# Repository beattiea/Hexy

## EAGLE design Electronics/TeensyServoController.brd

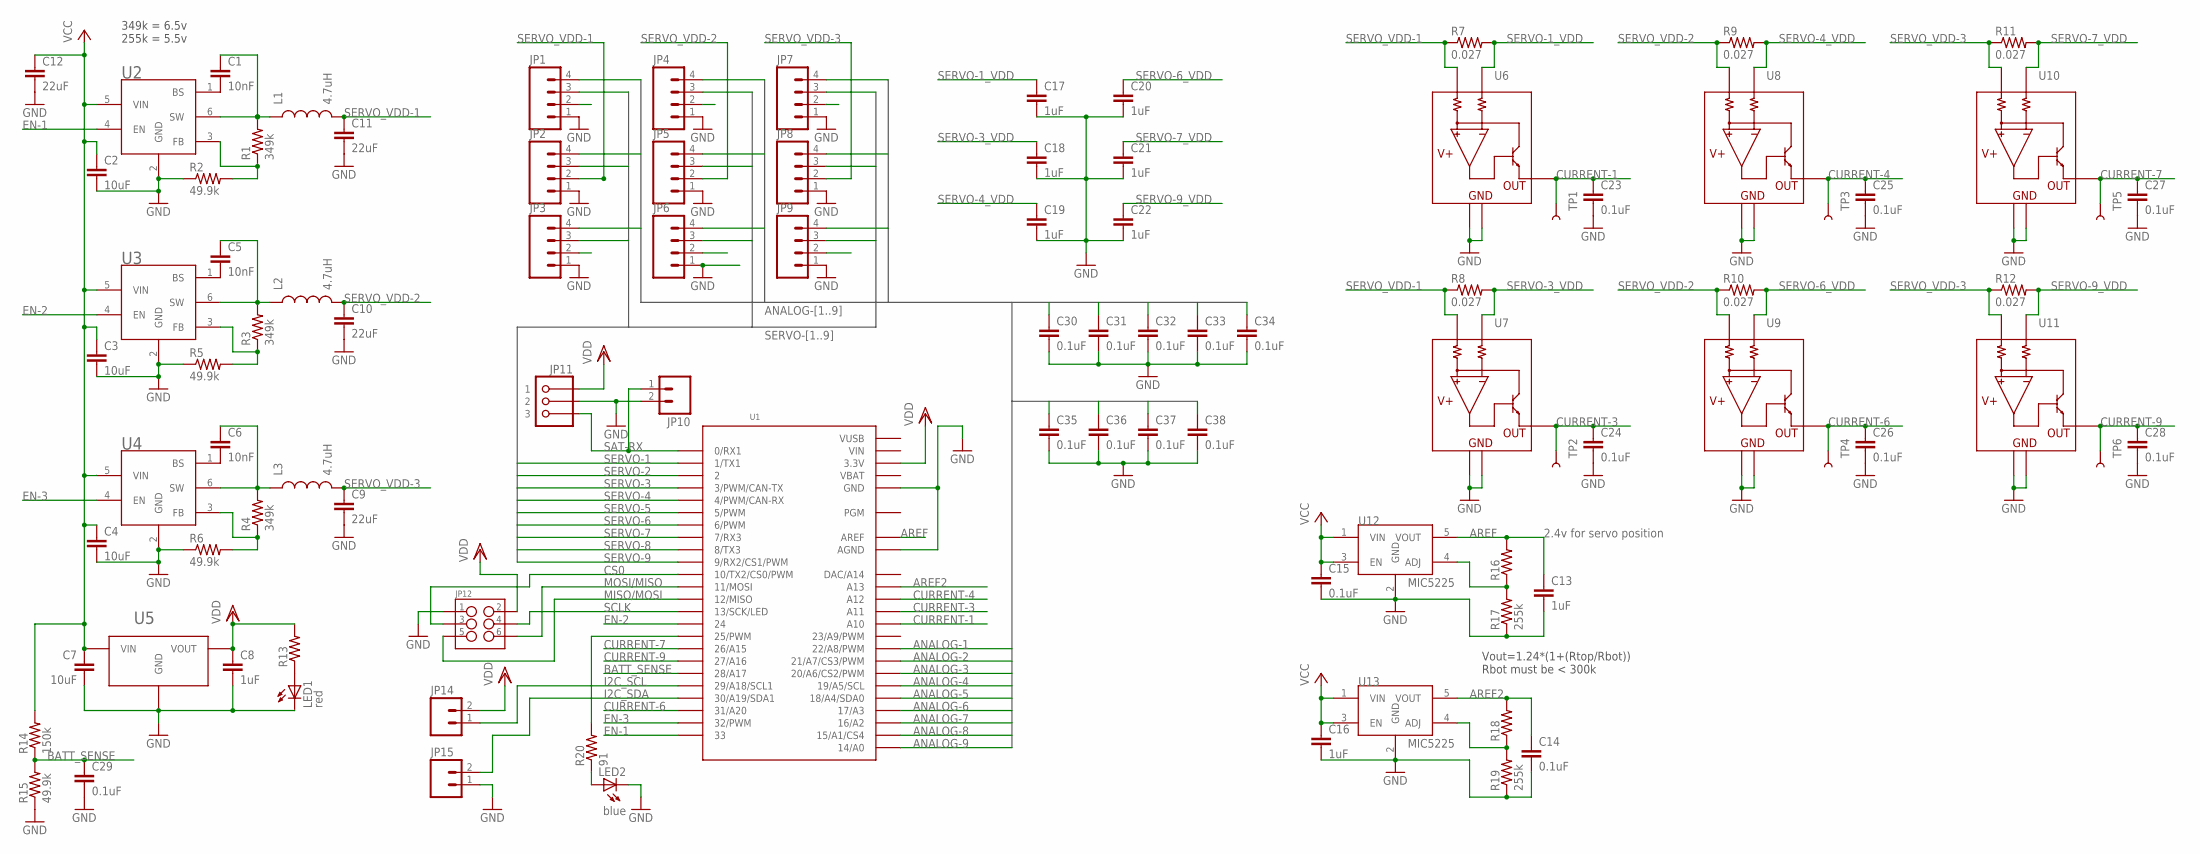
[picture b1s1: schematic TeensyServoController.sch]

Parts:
C1, C5, C6: 10nF; C0402
C2, C3, C4, C7: 10uF; C0805
C8, C13, C16, C17, C18, C19, C20, C21, C22: 1uF; C0603
C9, C10, C11: 22uF; C0603
C12: 22uF; C0805
C14, C23, C24, C25, C26, C27, C28, C29, C30, C31, C32, C33, C34, C35, C36, C37, C38: 0.1uF; C0402
C15: 0.1uF; C0603
JP1, JP2, JP3, JP4, JP5, JP6, JP7, JP8, JP9: M04PTH; 1X04
JP10, JP14, JP15: M02PTH; 1X02
JP11: 3-PIN_JST_ZH_PTH_CONNECTORRIGHT_ANGLE_PTH; 3-PIN_JST_ZH_CONNECTOR_TH
JP12: M03X22X3_SILK_SM; 2X3
L1, L2, L3: 4.7uH; 1008
LED1: red; LED-0603
LED2: blue; LED-0603
R1, R3, R4: 349k; R0402
R2, R5, R6, R15: 49.9k; R0402
R7, R8, R9, R10, R11, R12: 0.027; R0603
R13, R16, R18: R-US_R0402; R0402
R14: 150k; R0402
R17, R19: 255k; R0402
R20: 91; R0402
TP1, TP2, TP3, TP4, TP5, TP6: TEST-POINT3; PAD.03X.03
U1: TEENSY_3.1_ALLPINS; TEENSY_3.0_ALLPINS
U2, U3, U4: AP3211KTR-G1; SOT-23-6
U5: AP2210N-3.3TRG1; SOT23
U6, U7, U8, U9, U10, U11: TS1102; SOT23-5
U12, U13: MIC5225; SOT23-5

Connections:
ANALOG-1: C30.1, JP1.4, U1.22/A8 (22/A8/PWM)
ANALOG-2: C31.1, JP2.4, U1.21/A7 (21/A7/CS3/PWM)
ANALOG-3: C32.1, JP3.4, U1.20/A6 (20/A6/CS2/PWM)
ANALOG-4: C33.1, JP4.4, U1.19/A5 (19/A5/SCL)
ANALOG-5: C34.1, JP5.4, U1.18/A4 (18/A4/SDA0)
ANALOG-6: C35.1, JP6.4, U1.17/A3
ANALOG-7: C36.1, JP7.4, U1.16/A2
ANALOG-8: C37.1, JP8.4, U1.15/A1 (15/A1/CS4)
ANALOG-9: C38.1, JP9.4, U1.14/A0
AREF: C13.1, R16.2, U1.AREF, U12.5 (VOUT)
AREF2: C14.1, R18.2, U1.A13, U13.5 (VOUT)
BATT_SENSE: C29.1, R14.1, R15.2, U1.28 (28/A17)
CS0: JP12.3, U1.10 (10/TX2/CS0/PWM)
CURRENT-1: C23.1, TP1.P$1, U1.A10, U6.3 (OUT)
CURRENT-3: C24.1, TP2.P$1, U1.A11, U7.3 (OUT)
CURRENT-4: C25.1, TP3.P$1, U1.A12, U8.3 (OUT)
CURRENT-6: C26.1, TP4.P$1, U1.31 (31/A20), U9.3 (OUT)
CURRENT-7: C27.1, TP5.P$1, U1.26 (26/A15), U10.3 (OUT)
CURRENT-9: C28.1, TP6.P$1, U1.27 (27/A16), U11.3 (OUT)
EN-1: U1.33, U2.4 (EN)
EN-2: U1.24, U3.4 (EN)
EN-3: U1.32 (32/PWM), U4.4 (EN)
GND: C2.2, C3.2, C4.2, C7.2, C8.2, C9.2, C10.2, C11.2, C12.2, C13.2, C14.2, C15.2, C16.2, C17.2, C18.2, C19.2, C20.2, C21.2, C22.2, C23.2, C24.2, C25.2, C26.2, C27.2, C28.2, C29.2, C30.2, C31.2, C32.2, C33.2, C34.2, C35.2, C36.2, C37.2, C38.2, JP1.1, JP2.1, JP3.1, JP4.1, JP5.1, JP6.1, JP7.1, JP8.1, JP9.1, JP10.2, JP11.P$2 (2), JP12.1, JP15.1, LED1.C, LED2.C, R2.1, R5.1, R6.1, R15.1, R17.1, R19.1, U1.AGND, U1.GND, U1.GND1 (GND), U1.GND2 (GND), U2.2 (GND), U3.2 (GND), U4.2 (GND), U5.P$1 (GND), U6.1 (GND), U6.2, U7.1 (GND), U7.2, U8.1 (GND), U8.2, U9.1 (GND), U9.2, U10.1 (GND), U10.2, U11.1 (GND), U11.2, U12.2 (GND), U13.2 (GND)
I2C_SCL: JP14.1, U1.29 (29/A18/SCL1)
I2C_SDA: JP15.2, U1.30 (30/A19/SDA1)
MISO/MOSI: JP12.5, U1.12 (12/MISO)
MOSI/MISO: JP12.6, U1.11 (11/MOSI)
unnamed: LED1.A, R13.1
unnamed: R1.1, R2.2, U2.3 (FB)
unnamed: R16.1, R17.2, U12.4 (ADJ)
unnamed: R20.2, U1.25 (25/PWM)
unnamed: R18.1, R19.2, U13.4 (ADJ)
unnamed: LED2.A, R20.1
unnamed: C5.1, L2.P$1 (1), R3.2, U3.6 (SW)
unnamed: C1.1, L1.P$1 (1), R1.2, U2.6 (SW)
unnamed: C1.2, U2.1 (BS)
unnamed: R4.1, R6.2, U4.3 (FB)
unnamed: C5.2, U3.1 (BS)
unnamed: R3.1, R5.2, U3.3 (FB)
unnamed: C6.2, U4.1 (BS)
unnamed: C6.1, L3.P$1 (1), R4.2, U4.6 (SW)
SAT-RX: JP10.1, JP11.P$3 (3), U1.0 (0/RX1)
SCLK: JP12.4, U1.13 (13/SCK/LED)
SERVO-1: JP1.3, U1.1 (1/TX1)
SERVO-1_VDD: C17.1, JP1.2, R7.2, U6.4 (RS-)
SERVO-2: JP2.3, U1.2
SERVO-3: JP3.3, U1.3 (3/PWM/CAN-TX)
SERVO-3_VDD: C18.1, JP3.2, R8.2, U7.4 (RS-)
SERVO-4: JP4.3, U1.4 (4/PWM/CAN-RX)
SERVO-4_VDD: C19.1, JP4.2, R9.2, U8.4 (RS-)
SERVO-5: JP5.3, U1.5 (5/PWM)
SERVO-6: JP6.3, U1.6 (6/PWM)
SERVO-6_VDD: C20.1, JP6.2, R10.2, U9.4 (RS-)
SERVO-7: JP7.3, U1.7 (7/RX3)
SERVO-7_VDD: C21.1, JP7.2, R11.2, U10.4 (RS-)
SERVO-8: JP8.3, U1.8 (8/TX3)
SERVO-9: JP9.3, U1.9 (9/RX2/CS1/PWM)
SERVO-9_VDD: C22.1, JP9.2, R12.2, U11.4 (RS-)
SERVO_VDD-1: C11.1, JP2.2, L1.P$2 (2), R7.1, R8.1, U6.5 (RS+), U7.5 (RS+)
SERVO_VDD-2: C10.1, JP5.2, L2.P$2 (2), R9.1, R10.1, U8.5 (RS+), U9.5 (RS+)
SERVO_VDD-3: C9.1, JP8.2, L3.P$2 (2), R11.1, R12.1, U10.5 (RS+), U11.5 (RS+)
VBAT: U1.VBAT
VCC: C2.1, C3.1, C4.1, C7.1, C12.1, C15.1, C16.1, R14.2, U2.5 (VIN), U3.5 (VIN), U4.5 (VIN), U5.P$3 (VIN), U12.1 (VIN), U12.3 (EN), U13.1 (VIN), U13.3 (EN)
VDD: C8.1, JP11.P$1 (1), JP12.2, JP14.2, R13.2, U1.3.3V, U1.3.3V1 (3.3V), U1.3.3V2 (3.3V), U1.VIN, U5.P$2 (VOUT)
VUSB: U1.VUSB

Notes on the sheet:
349k = 6.5v 255k = 5.5v
Vout=1.24*(1+(Rtop/Rbot)) Rbot must be < 300k
2.4v for servo position

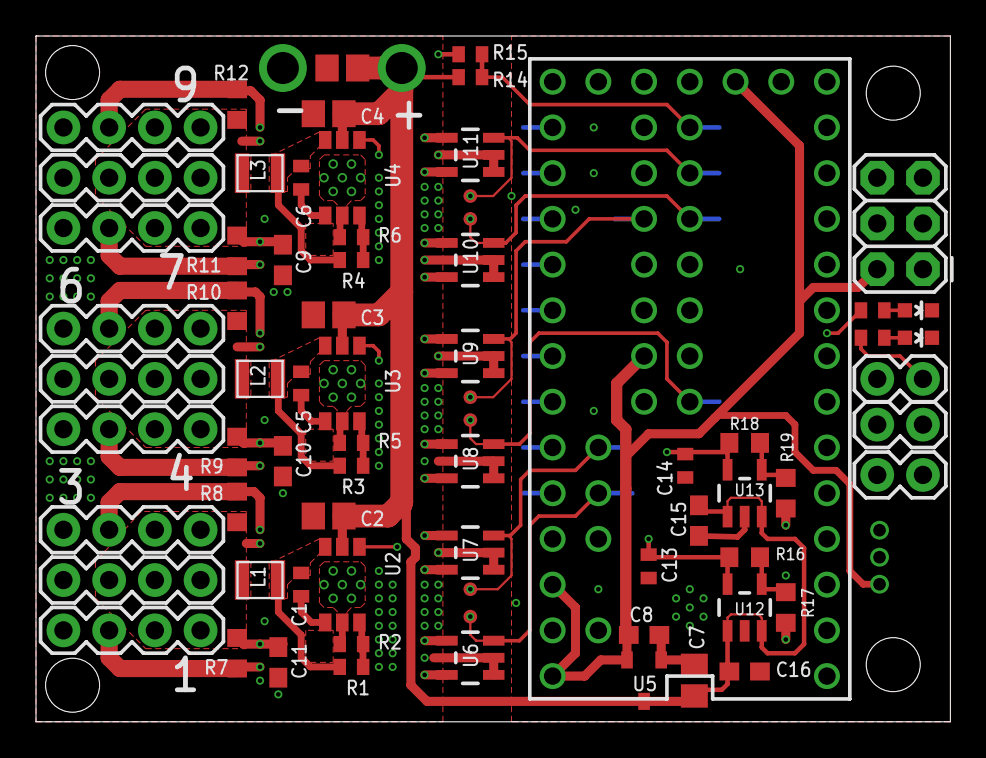
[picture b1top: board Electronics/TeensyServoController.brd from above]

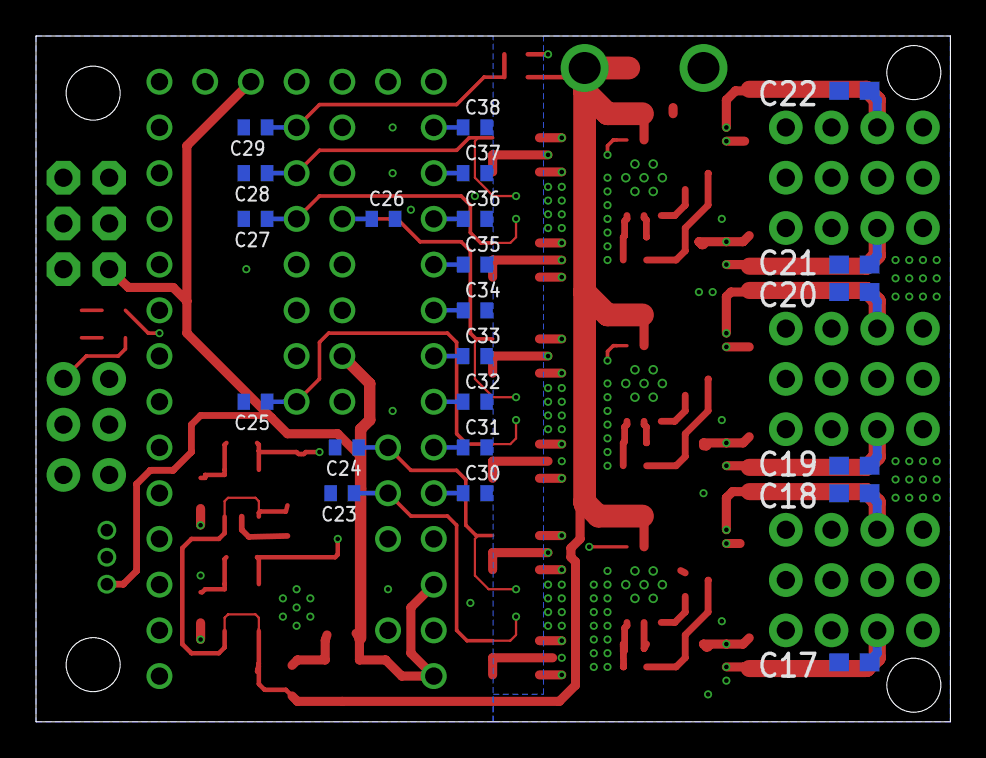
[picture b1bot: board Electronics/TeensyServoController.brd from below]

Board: 4 copper layers, 50.8 x 38.1 mm, 96 parts (22 on the bottom side), 63 nets.

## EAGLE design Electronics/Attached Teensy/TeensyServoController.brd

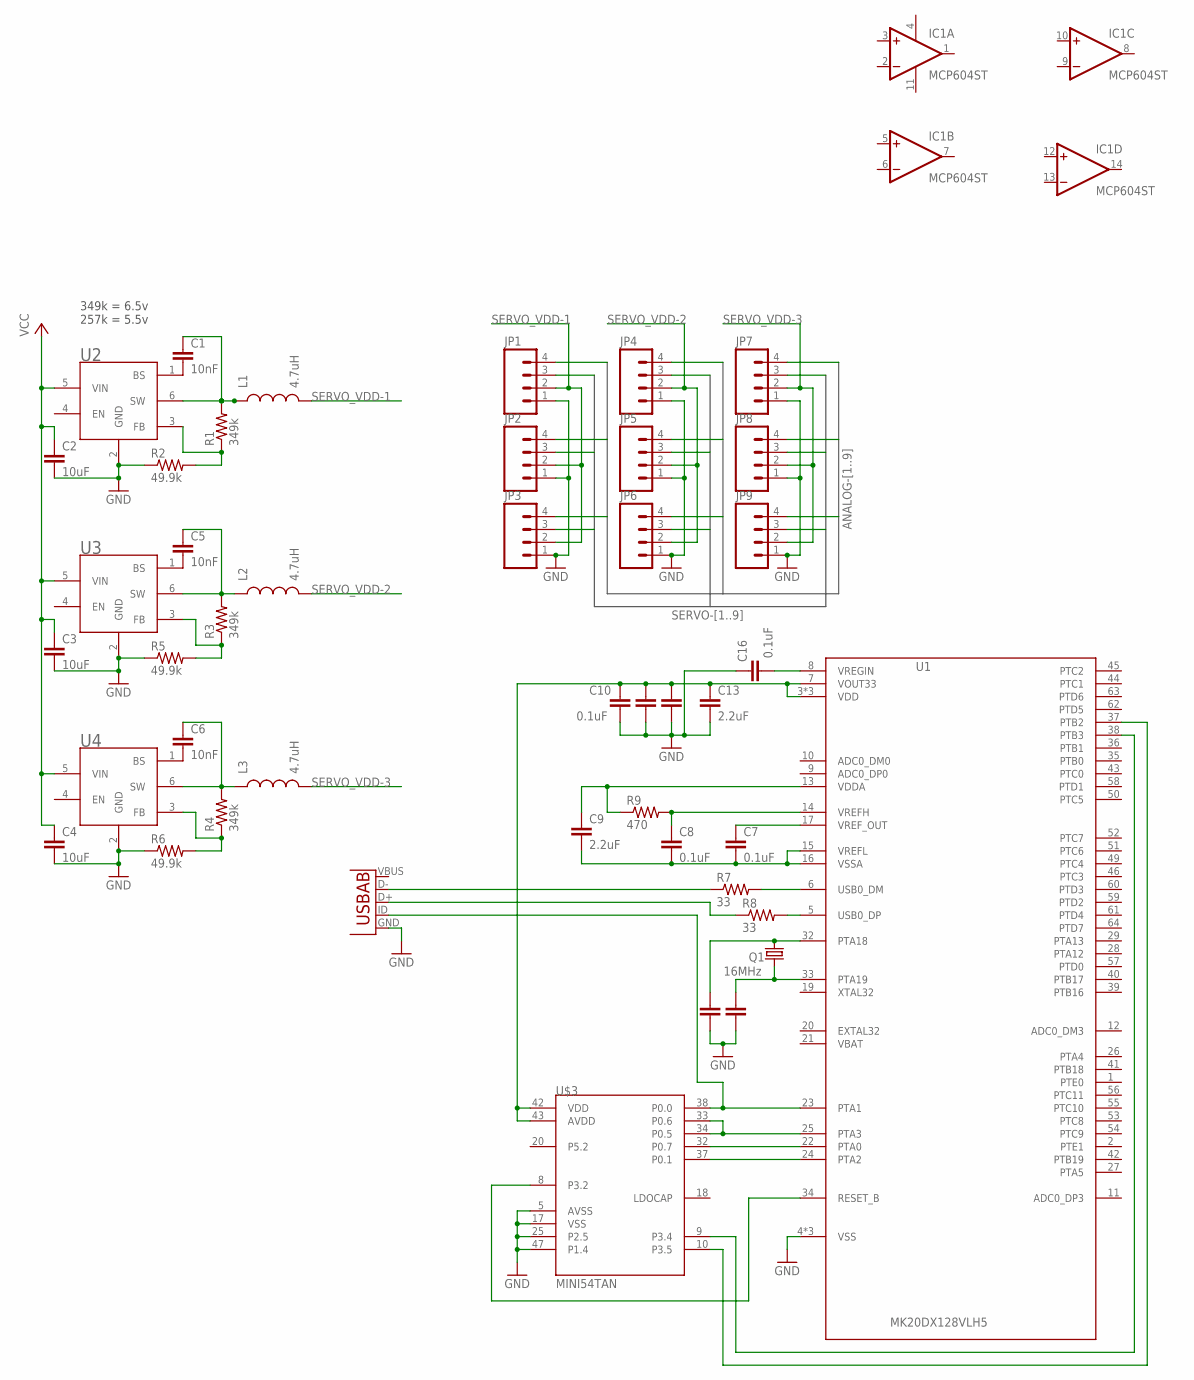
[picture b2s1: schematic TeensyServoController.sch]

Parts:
C1, C5, C6: 10nF; C0402
C2, C3, C4: 10uF; C0805
C7, C8, C10, C11, C12, C14, C15, C16: 0.1uF; C0402
C9, C13: 2.2uF; C0603
IC1: MCP604ST; TSSOP14
JP1, JP2, JP3, JP4, JP5, JP6, JP7, JP8, JP9: M04LOCK; 1X04_LOCK
L1, L2, L3: 4.7uH; CR75
Q1: 16MHz; CTS406
R1, R3, R4: 349k; R0402
R2, R5, R6: 49.9k; R0402
R7, R8: 33; R0402
R9: 470; R0402
U1: MK20DX128VLH5
U2, U3, U4: AP3211_SWITCHING_REGULATOR; SOT-23-6
U5: USB-AB; USB-AB-MICRO-SMD
U$3: MINI54TAN

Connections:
ANALOG-1: JP1.4
ANALOG-2: JP2.4
ANALOG-3: JP3.4
ANALOG-4: JP4.4
ANALOG-5: JP5.4
ANALOG-6: JP6.4
ANALOG-7: JP7.4
ANALOG-8: JP8.4
ANALOG-9: JP9.4
GND: C2.2, C3.2, C4.2, C10.2, C11.2, C12.2, C13.2, C14.2, C15.2, C16.1, JP1.1, JP2.1, JP3.1, JP4.1, JP5.1, JP6.1, JP7.1, JP8.1, JP9.1, R2.1, R5.1, R6.1, U1.4 (VSS), U1.31 (VSS), U1.47 (VSS), U2.2 (GND), U3.2 (GND), U4.2 (GND), U5.GND, U$3.5 (AVSS), U$3.17 (VSS), U$3.25 (P2.5), U$3.47 (P1.4)
unnamed: U1.23 (PTA1), U5.ID (USBID), U$3.38 (P0.0)
unnamed: U1.25 (PTA3), U$3.33 (P0.6), U$3.34 (P0.5)
unnamed: U1.22 (PTA0), U$3.32 (P0.7)
unnamed: U1.24 (PTA2), U$3.37 (P0.1)
unnamed: U1.37 (PTB2), U$3.10 (P3.5)
unnamed: R1.1, R2.2, U2.3 (FB)
unnamed: U1.38 (PTB3), U$3.9 (P3.4)
unnamed: R8.1, U5.D+
unnamed: R7.1, U5.D-
unnamed: C5.1, L2.P$1 (1), R3.2, U3.6 (SW)
unnamed: R7.2, U1.6 (USB0_DM)
unnamed: C1.1, L1.P$1 (1), R1.2, U2.6 (SW)
unnamed: C1.2, U2.1 (BS)
unnamed: R8.2, U1.5 (USB0_DP)
unnamed: R4.1, R6.2, U4.3 (FB)
unnamed: C5.2, U3.1 (BS)
unnamed: R3.1, R5.2, U3.3 (FB)
unnamed: C6.2, U4.1 (BS)
unnamed: C6.1, L3.P$1 (1), R4.2, U4.6 (SW)
unnamed: C14.1, Q1.3 (2), U1.32 (PTA18)
unnamed: C15.1, Q1.1, U1.33 (PTA19)
unnamed: C16.2, U1.8 (VREGIN)
unnamed: C9.1, R9.1, U1.13 (VDDA)
unnamed: C7.2, C8.2, C9.2, U1.15 (VREFL), U1.16 (VSSA)
unnamed: C7.1, U1.17 (VREF_OUT)
unnamed: C8.1, R9.2, U1.14 (VREFH)
unnamed: U1.34 (RESET_B), U$3.8 (P3.2)
unnamed: C10.1, C11.1, C12.1, C13.1, U1.3 (VDD), U1.7 (VOUT33), U1.30 (VDD), U1.48 (VDD), U$3.42 (VDD), U$3.43 (AVDD)
SERVO-1: JP1.3
SERVO-2: JP2.3
SERVO-3: JP3.3
SERVO-4: JP4.3
SERVO-5: JP5.3
SERVO-6: JP6.3
SERVO-7: JP7.3
SERVO-8: JP8.3
SERVO-9: JP9.3
SERVO_VDD-1: JP1.2, JP2.2, JP3.2, L1.P$2 (2)
SERVO_VDD-2: JP4.2, JP5.2, JP6.2, L2.P$2 (2)
SERVO_VDD-3: JP7.2, JP8.2, JP9.2, L3.P$2 (2)
V+: IC1.4 (V+)
V-: IC1.11 (V-)
VCC: C2.1, C3.1, C4.1, U2.5 (VIN), U3.5 (VIN), U4.5 (VIN)

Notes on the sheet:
349k = 6.5v 257k = 5.5v

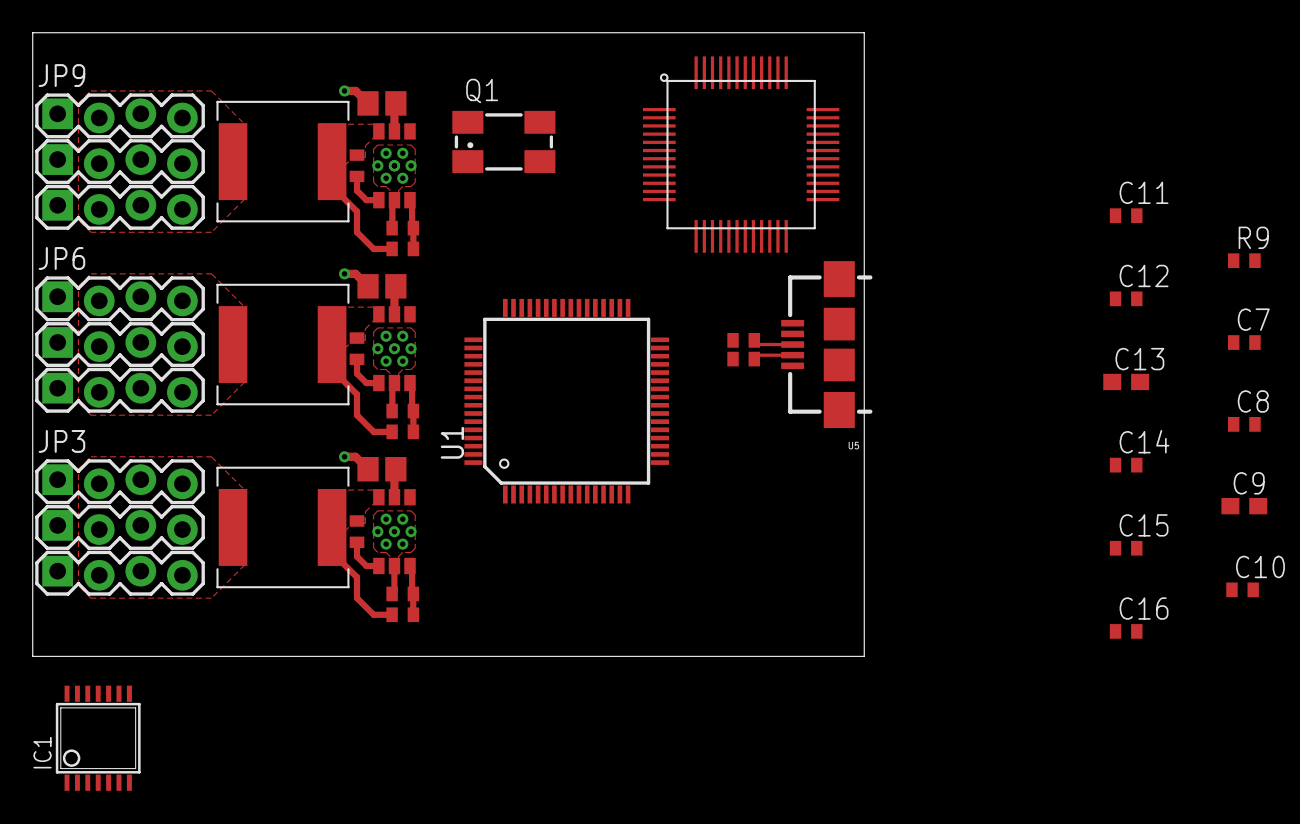
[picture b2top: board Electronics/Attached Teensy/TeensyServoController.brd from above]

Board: 2 copper layers, 50.8 x 38.1 mm, 45 parts (0 on the bottom side), 33 nets.

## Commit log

2015-03-06 Added propellers and motors to files
2015-03-06 Added motor/propeller assemblies to CAD
2015-03-06 Deleted head from Hexy.SLDASM
2015-03-06 Tried to update servo mass, no success
2015-03-10 Added Electronics Folder
2015-03-11 Tried to simulate load on body base
    Solidworks refused to cooperate
2015-03-12 Just resaved file as newest file type
2015-03-12 Continued Work on Teensy servo controller
2015-03-17 Servo controller mostly done (no I sense)
2015-03-31 Electronics finalized and ordered
2015-03-31 Added MG90S metal gear servo CAD part
2015-04-01 Added two new assemblies for flying version
    New metal gear servo leg
    New main body
2015-04-01 Slight body modifications
    Slightly modified thigh middle piece
    Added some screws to main assembly
2015-04-03 Added metal gear part DXF's
    They need to be updated to compensate for the loss of material due to
    the laser
2015-04-03 Modified files for laser cutting
2015-04-03 Preliminary final laser models for thigh
2015-04-05 Added power distribution PCB CAD file
2015-04-05 Finalized values for most components on PCBs
2015-04-06 Started modifying electronics mounting plate
    Also added battery holder to flying assembly
2015-04-08 Added 10mm M3 machine screw
2015-04-08 Added servo controller PCB
2015-04-08 Updated legs to use 10mm M3 screws where necessary
2015-04-08 Added controller PCB mount assembly
2015-04-10 Updated PCB design after receiving rev 1
    Fixed regulator footprint
    Changed a few part packages
2015-04-10 Added software folder and PCB test program
2015-04-20 Added brainstorming file. Use Xmind (free)
2015-04-21 Tested Github
2015-04-22 Added projection lines for mounts
2015-04-22 Screw Size Change
    Changed Thigh Bottom holes from 2.5 mm to 2.0 mm. Updated relevant
    files. (laser DXF, and SLDPRT)
2015-04-22 Created rough motor mount arm
2015-04-22 Modified body_pivot
    Modified part to mount motors
2015-04-22 Updated motor mount arm
2015-04-22 Updated the motor screw holes
2015-04-22 Increased PCB CAD model detail
2015-04-22 Flight motor mount work
    Fixed motor_mount_arm holes, added motor mount assembly
2015-04-23 Added .DXF file for revised body_pivot
2015-04-23 Added fillets to thigh_middle
    Added to decrease stress concentration points and improve laser cutting
2015-04-23 Motor mount arm refined
    Added lightening holes, wire pass-throughs, screw clearance holes, and
    fillets to reduce stress load
2015-04-23 Rotated motor mount screw holes by 90 degrees
    Now motor wires pass through hole in motor_mount_arm
2015-04-23 updated dxf
    motor mount arm
2015-04-24 Laser part hips updated
2015-04-24 Added a simple landing leg
2015-04-24 Added flight controller mount
2015-04-24 Tweaked hole sizes for flight controller mounting
2015-04-25 Added a motor ESC mount and updated landing leg
2015-04-28 Updated propeller size
2015-04-28 Added motor controller
    ZTW Spider 12A Opto
2015-04-28 Updated motor mount arm to mount ESC
2015-04-28 Redesigned body_horn
    Added mounts for power distro pcb and servo power supply on body_horn
2015-04-29 New dimensions for mounting
    controller arm mount dimensions changed.
    Base horn mount dimensions changed
2015-05-01 Changed Battery Door
2015-05-12 Beefed up landing legs
    The old ones were flimsy and broke too easily

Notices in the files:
parts and their libraries:
SparkFun-Connectors: Licensing: CC v3.0 Share-Alike You are welcome to use this library for commercial purposes.
